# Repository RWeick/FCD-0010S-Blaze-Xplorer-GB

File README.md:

# FCD-0010S-Blaze-Xplorer-GB
The kicad files and binary firmware for the Blaze Xplorer GB. The diodes are used in series to create the necessary 3.3v expected by the Altera EPM3064. The footprints for a VREG exist below the diode pads, you may use either a 3.3 VREG or the diodes.

PCB Thickness: 0.8 mm

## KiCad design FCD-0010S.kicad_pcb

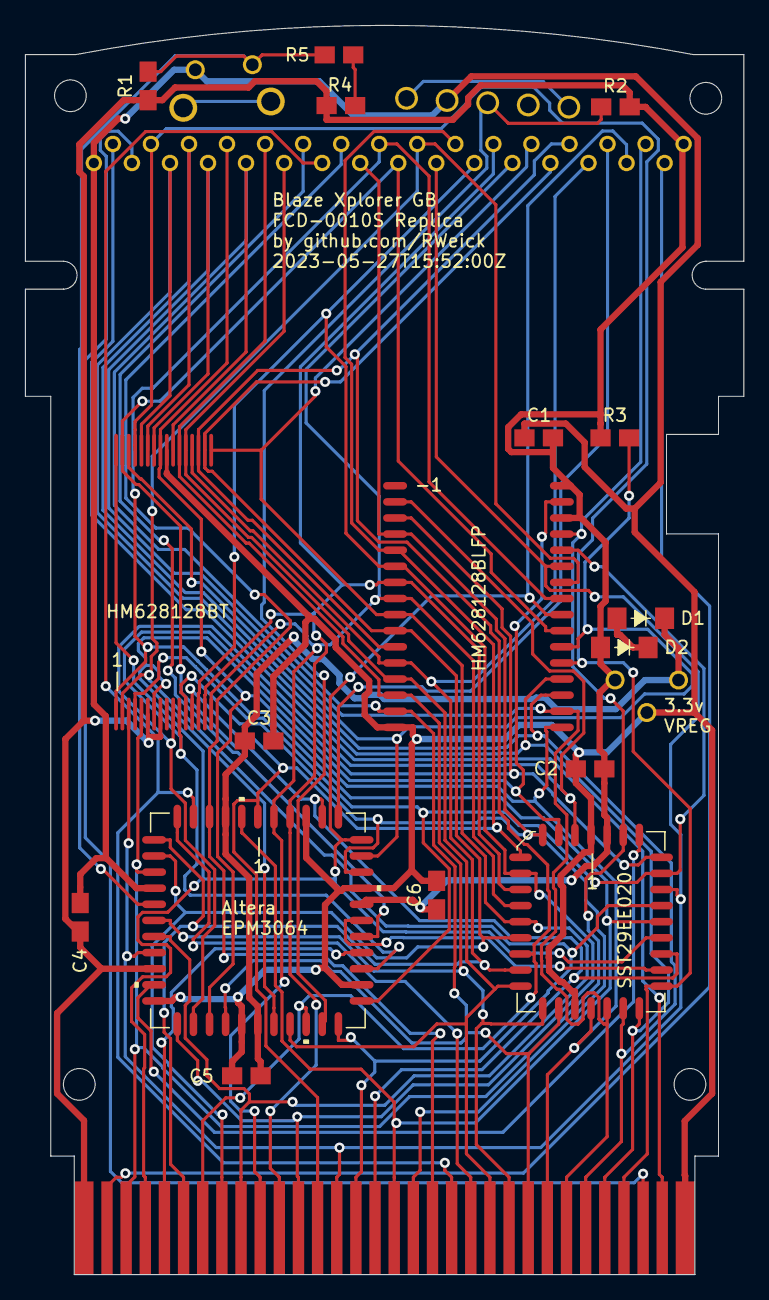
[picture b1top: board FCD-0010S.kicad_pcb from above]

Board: 2 copper layers, 56.7 x 98.5 mm, 26 parts (0 on the bottom side), 46 nets.

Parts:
C1, C3, C4, C5, C6: 100 nF 0805; SMD Cap Res
C2: 215 nF 0805; SMD Cap Res
D1, D2: DIODE; Diode
Hole1, Hole2, Hole3, Hole4: MountingHole_2.5mm
J1: Cart_Edge_Connector; Edge Connector
J2: Game_Edge_Connector; Cartridge Connector
R1, R2, R3: 100k Ohm 0805; SMD Cap Res
R4, R5: Unused 0805; SMD Cap Res
S1: Slide Switch; Switch
SW1: Push Button; Button
U1: EPM3064ALC44-10N
U2: SST29EE020; SST 29EE020
U3: HM628128BLFP-8
U4: HM628128BLFP Normal TSOP
U5: 3.3 VREG Unused; 3.3 VREG

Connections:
/A0: J1.6 (A0), J2.6 (A0), U1.7 (TDI), U2.12 (A0), U3.12 (A0), U4.20 (A0)
/A1: J1.7 (A1), J2.7 (A1), U1.26 (IO_C_36), U2.11 (A1), U3.11 (A1), U4.19 (A1)
/A2: J1.8 (A2), J2.8 (A2), U1.8 (IO_A_5), U2.10 (A2), U3.10 (A2), U4.18 (A2)
/A3: J1.9 (A3), J2.9 (A3), U1.13 (TMS), U2.9 (A3), U3.9 (A3), U4.17 (A3)
/A4: J1.10 (A4), J2.10 (A4), U1.44 (INPUT/OE1), U2.8 (A4), U3.8 (A4), U4.16 (A4)
/A5: J1.11 (A5), J2.11 (A5), U1.43 (INPUT/GCLK1), U2.7 (A5), U3.7 (A5), U4.15 (A5)
/A6: J1.12 (A6), J2.12 (A6), U1.18 (IO_B_21), U2.6 (A6), U3.6 (A6), U4.14 (A6)
/A7: J1.13 (A7), J2.13 (A7), U1.1 (INPUT/GCLRN), U2.5 (A7), U3.5 (A7), U4.13 (A7)
/A8: J1.14 (A8), J2.14 (A8), U1.14 (IO_B_30), U2.27 (A8), U3.27 (A8), U4.3 (A8)
/A9: J1.15 (A9), J2.15 (A9), U1.28 (IO_C_40), U2.26 (A9), U3.26 (A9), U4.2 (A9)
/A10: J1.16 (A10), J2.16 (A10), U1.41 (IO_D_64), U2.23 (A10), U3.23 (A10), U4.31 (A10)
/A11: J1.17 (A11), J2.17 (A11), U1.2 (INPUT/OE2/GCLK2), U2.25 (A11), U3.25 (A11), U4.1 (A11)
/A12: J1.18 (A12), J2.18 (A12), U1.37 (IO_D_53), U2.4 (A12), U3.4 (A12), U4.12 (A12)
/A13.Internal: U1.29 (IO_C_41), U2.28 (A13), U3.28 (A13), U4.4 (A13)
/A13.Sys: J1.19 (A13), J2.19 (A13), U1.4 (IO_A_16)
/A14.Internal: U1.31 (IO_C_46), U2.29 (A14), U3.3 (A14), U4.11 (A14)
/A14.Sys: J1.20 (A14), J2.20 (A14), U1.5 (IO_A_14)
/A15.Game: J2.21 (A15), U1.33 (IO_D_49)
/A15.Internal: U1.24 (IO_C_33), U2.3 (A15), U3.31 (A15), U4.7 (A15)
/A15.Sys: J1.21 (A15), U1.6 (IO_A_11)
/A16.Internal: U1.19 (IO_B_20), U2.2 (A16), U3.2 (A16), U4.10 (A16)
/A17.SST: U1.16 (IO_B_25), U2.30 (A17)
/Audio: J1.31 (Audio), J2.31 (Audio)
/Button: R1.2, R5.1, SW1.2, U1.11 (IO_A_3)
/CE.SST: U1.34 (IO_D_51), U2.22 (CE#)
/CS.Game: J2.5 (CS), U1.40 (IO_D_62)
/CS.Sys: J1.5 (CS), U1.32 (TCK)
/Clock: J1.2 (Clock), J2.2 (Clock)
/D0: J1.22 (Data_0), J2.22 (Data_0), U1.25 (IO_C_35), U2.13 (DQ0), U3.13 (I/O_0), U4.21 (I/O_0)
/D1: J1.23 (Data_1), J2.23 (Data_1), U1.12 (IO_A_1), U2.14 (DQ1), U3.14 (I/O_1), U4.22 (I/O_1)
/D1.VCC: C3.1, C5.2, D1.2 (A), U1.3 (VCCINT3-3VONLY), U1.23 (VCCINT3-3VONLY_2), U5.3 (VO)
/D2: J1.24 (Data_2), J2.24 (Data_2), U1.21 (IO_B_17), U2.15 (DQ2), U3.15 (I/O_2), U4.23 (I/O_2)
/D3: J1.25 (Data_3), J2.25 (Data_3), U1.20 (IO_B_19), U2.17 (DQ3), U3.17 (I/O_3), U4.25 (I/O_3)
/D4: J1.26 (Data_4), J2.26 (Data_4), U2.18 (DQ4), U3.18 (I/O_4), U4.26 (I/O_4)
/D5: J1.27 (Data_5), J2.27 (Data_5), U2.19 (DQ5), U3.19 (I/O_5), U4.27 (I/O_5)
/D6: J1.28 (Data_6), J2.28 (Data_6), U2.20 (DQ6), U3.20 (I/O_6), U4.28 (I/O_6)
/D7: J1.29 (Data_7), J2.29 (Data_7), U2.21 (DQ7), U3.21 (I/O_7), U4.29 (I/O_7)
/GND: C1.1, C2.1, C3.2, C4.2, C5.1, C6.2, J1.32 (GND), J2.32 (GND), S1.1 (A), SW1.1, U1.10 (GNDIO), U1.17 (GNDIO), U1.22 (GNDINT), U1.30 (GNDIO), U1.36 (GNDIO), U1.42 (GNDINT), U2.1 (N/C), U2.16 (GND), U3.16 (VSS), U4.24 (VSS), U5.2 (GND)
/Read: J1.4 (Read), J2.4 (Read), U1.39 (IO_D_57), U2.24 (OE#), U3.24 (OE), U4.32 (OE)
/Reset: J1.30 (Reset), J2.30 (Reset)
/SRAM.CS1: R3.2, U1.38 (TDO), U3.22 (CS1), U4.30 (CS1)
/Switch: R2.1, S1.2 (B), U1.27 (IO_C_37)
/VCC: C1.2, C2.2, C4.1, C6.1, D2.1 (K), J1.1 (+5V), J2.1 (+5V), R1.1, R2.2, R3.1, R4.1, U1.15 (VCCIO2-5VOR3-3V), U1.35 (VCCIO2-5VOR3-3V_2), U2.32 (VCC), U3.30 (CS2), U3.32 (VCC), U4.6 (CS2), U4.8 (VCC), U5.1 (VI)
/Write: J1.3 (Write), J2.3 (Write), U1.9 (IO_A_4), U2.31 (WE#), U3.29 (WE), U4.5 (WE)
unnamed: D1.1 (K), D2.2 (A)
unnamed: R4.2, R5.2
